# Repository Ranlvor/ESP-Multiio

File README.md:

Mechanical
==========

Achtung: Eines der Haltelöscher ist nicht 5mm / 5mm vom Rand entfernt! Das 3D-Druck-Gehäuse geht davon aus, dass alle Löscher 5mm/5mm vom Rand entfernt sind und muss noch angepasst werden.

BOM
===

zwingend Nötig
--------------

Bezeichnung | Beschreibung
------------|--------------
U1          | Wemos D1 Mini

notwendig für LEDs und Schalter
-------------------------------

Bezeichnung                    | Beschreibung                        | Package
-------------------------------|-------------------------------------|-----------------
D1, D2, D3, D4, D5, D6, D7, D8 | LEDs                                | 3mm Through Hole
R1, R2, R3, R4, R5, R6, R7, R8 | Vorwiderstände passend zu den LEDs  | 1206 SMD
U2                             | MCP23017                            | DIP-28
C1                             | Kondensator ca. 100 nF              | 1206 SMD

notwendig für IR receive (getestet, hat nicht funktioniert)
-----------------------------------------------------------

Bezeichnung | Beschreibung                        | Package
------------|-------------------------------------|-----------------
U4          | TL1838                              | TSOP1838
C2          | Kondensator ca. 100 nF              | 1206 SMD
R11         | Widerstand 33 kΩ                    | 1206 SMD
R12         | Widerstand 100 Ω                    | 1206 SMD

notwendig für IR send (ungetestet)
----------------------------------

Bezeichnung | Beschreibung                        | Package
------------|-------------------------------------|-----------------
D-IR1       | IR-LED                              | 3mm Through Hole
Q1          | NPN-Transistor (z.B. BC337)         | TO-92
R10         | Widerstand 53 Ω                     | 1206 SMD
R9          | Widerstand 2.1 kΩ                   | 1206 SMD

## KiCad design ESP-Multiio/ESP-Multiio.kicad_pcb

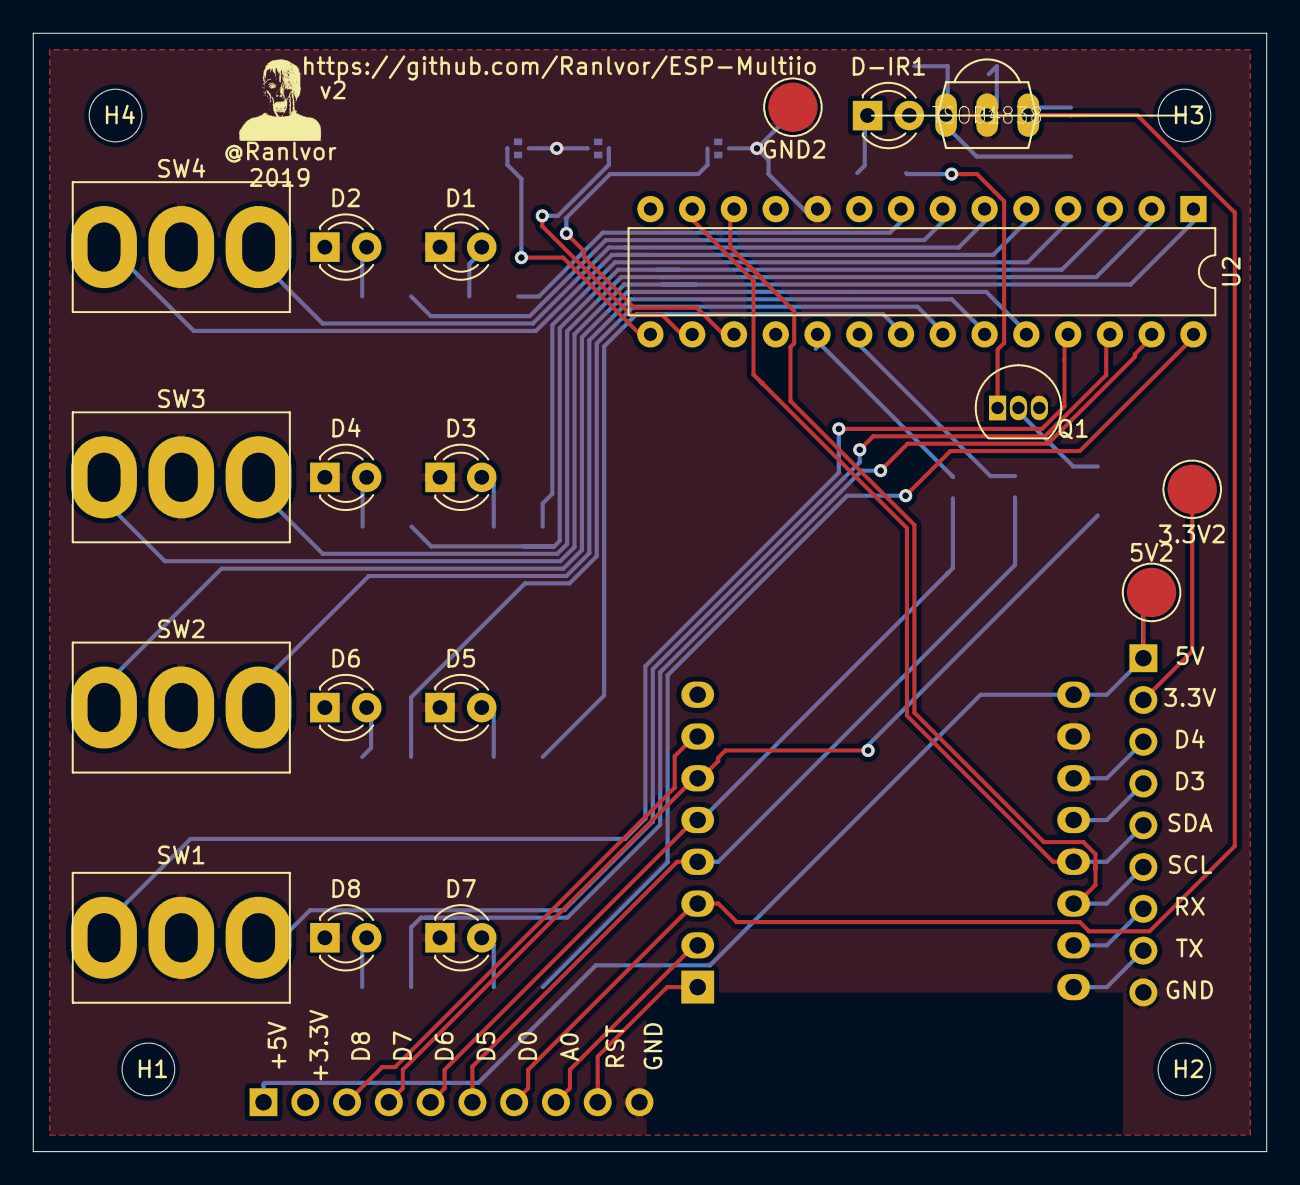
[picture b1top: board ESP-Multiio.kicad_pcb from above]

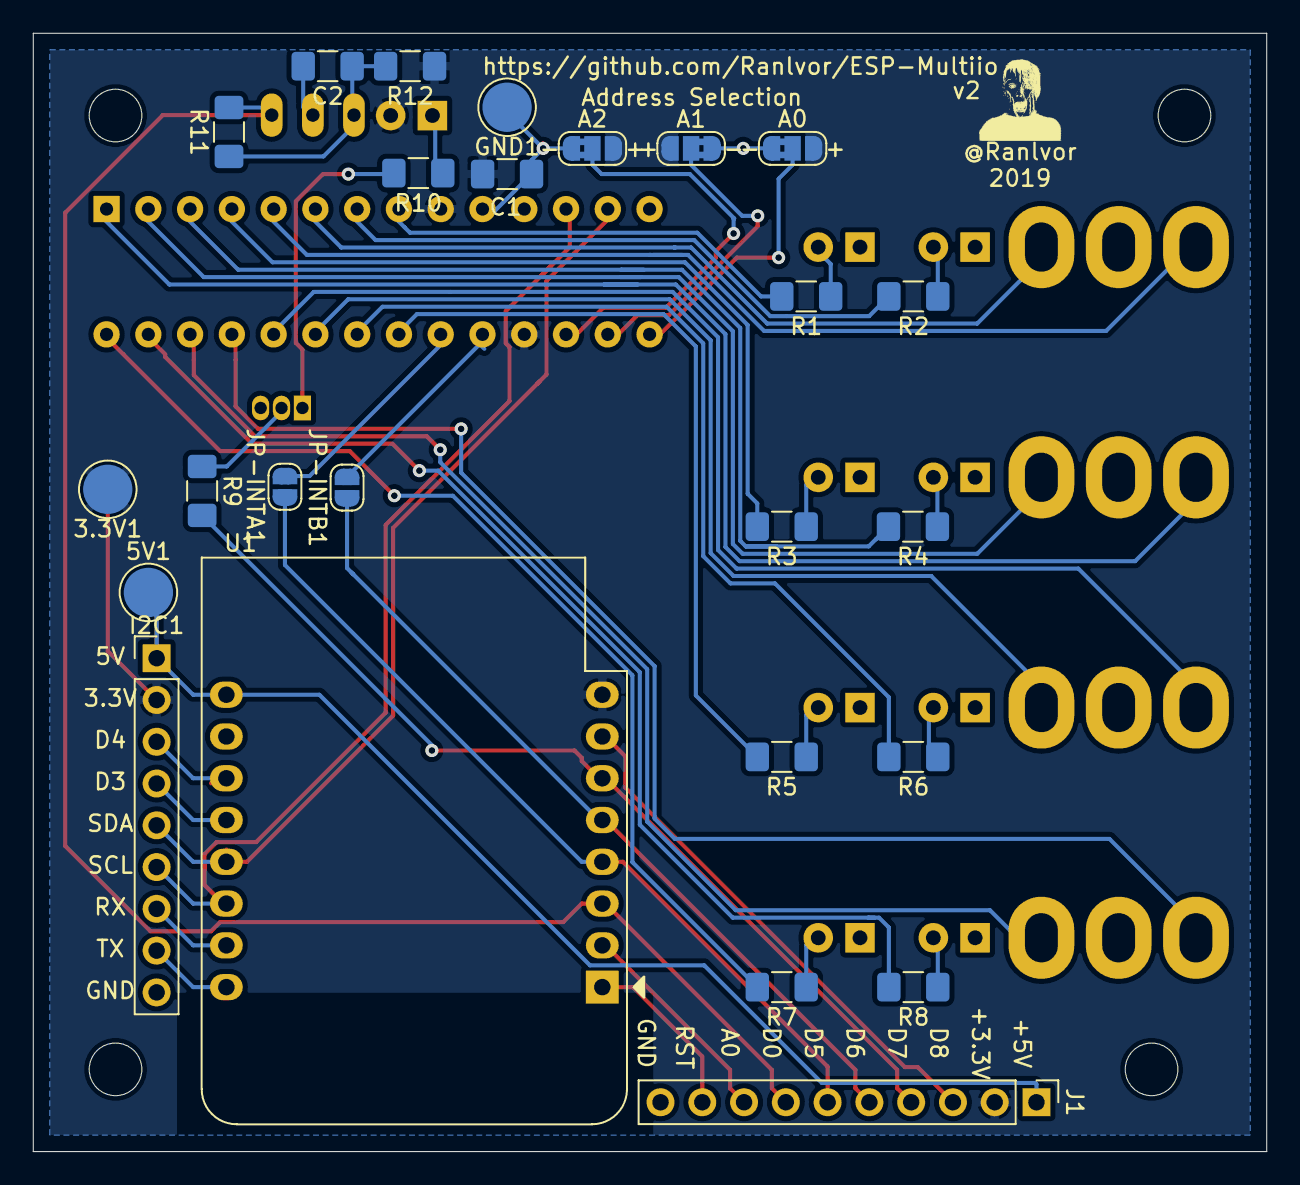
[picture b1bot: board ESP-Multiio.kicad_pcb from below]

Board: 2 copper layers, 75.0 x 68.0 mm, 48 parts (25 on the bottom side), 49 nets.

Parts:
3.3V1, 3.3V2, 5V1, 5V2: TestPoint; TestPoint_Pad_D3.0mm
A0, A1, A2: SolderJumper; SolderJumper-3_P1.3mm_Bridged2Bar12_RoundedPad1.0x1.5mm_Num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
C1, C2: 100 nF; C_1206_3216Metric_Pad1.42x1.75mm_HandSolder
D1, D2, D3, D4, D5, D6, D7, D8: LED; LED_D3.0mm
D-IR1: LED; LED_D3.0mm
GND1, GND2: TestPoint; TestPoint_Pad_D3.0mm
H1, H2, H3, H4: MountingHole; MountingHole_3.2mm_M3
I2C1: Conn_01x09; PinHeader_1x09_P2.54mm_Vertical
J1: Conn_01x10; PinHeader_1x10_P2.54mm_Vertical
JP-INTA1: SolderJumper_2_Open; SolderJumper-2_P1.3mm_Open_RoundedPad1.0x1.5mm
JP-INTB1: SolderJumper_2_Open; SolderJumper-2_P1.3mm_Open_RoundedPad1.0x1.5mm
Q1: BC337; TO-92_Inline
R1, R2, R3, R4, R5, R6, R7, R8: R; R_1206_3216Metric_Pad1.42x1.75mm_HandSolder
R9: 2.1kΩ; R_1206_3216Metric_Pad1.42x1.75mm_HandSolder
R10: 53 Ω; R_1206_3216Metric_Pad1.42x1.75mm_HandSolder
R11: 33 kΩ; R_1206_3216Metric_Pad1.42x1.75mm_HandSolder
R12: 100Ω; R_1206_3216Metric_Pad1.42x1.75mm_HandSolder
SW1, SW2, SW3, SW4: SW_SPDT_MSM; MTS-103
U1: WeMos_D1_mini; WEMOS_D1_mini_light
U2: MCP23017_SP; DIP-28_W7.62mm
U4: TSOP1838; TSOP18XX

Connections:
+3V3: 3.3V1.1, 3.3V2.1, A0.3, A1.3, A2.3, C1.1, D-IR1.2, I2C1.2, J1.2, R12.1, U1.8, U2.9, U2.18
+5V: 5V1.1, 5V2.1, I2C1.1, J1.1, U1.9
/A0: J1.8, U1.2
/D0: J1.7, R11.2, U1.3, U4.OUT
/D5: J1.6, JP-INTA1.1, U1.4
/D6: J1.5, JP-INTB1.1, U1.5
/D7: J1.4, R9.2, U1.6
/D8: J1.3, U1.7
/GPA0: R1.2, U2.8
/GPA1: R2.2, U2.7
/GPA2: SW4.1, U2.6
/GPA3: SW4.3, U2.5
/GPA4: R3.2, U2.4
/GPA5: R4.2, U2.3
/GPA6: SW3.1, U2.2
/GPA7: SW3.3, U2.1
/GPB0: R7.2, U2.28
/GPB1: R8.2, U2.27
/GPB2: SW1.1, U2.26
/GPB3: SW1.3, U2.25
/GPB4: SW2.3, U2.24
/GPB5: SW2.1, U2.23
/GPB6: R6.2, U2.22
/GPB7: R5.2, U2.21
/RST: J1.9, U1.1
/RX: I2C1.7, U1.15
/TX: I2C1.8, U1.16
D3: I2C1.4, U1.12
D4: I2C1.3, U1.11
GND: A0.1, A1.1, A2.1, C1.2, C2.2, D1.1, D2.1, D3.1, D4.1, D5.1, D6.1, D7.1, D8.1, GND1.1, GND2.1, I2C1.9, J1.10, Q1.3, SW1.2, SW2.2, SW3.2, SW4.2, U1.10, U2.10, U4.GND
unnamed: A0.2, U2.15
unnamed: A1.2, U2.16
unnamed: A2.2, U2.17
unnamed: C2.1, R11.1, R12.2, U4.VCC
unnamed: D1.2, R1.1
unnamed: D2.2, R2.1
unnamed: D3.2, R3.1
unnamed: D4.2, R4.1
unnamed: D5.2, R5.1
unnamed: D6.2, R6.1
unnamed: D7.2, R7.1
unnamed: D8.2, R8.1
unnamed: D-IR1.1, R10.1
unnamed: JP-INTA1.2, U2.20
unnamed: JP-INTB1.2, U2.19
unnamed: Q1.1, R10.2
unnamed: Q1.2, R9.1
SCL: I2C1.6, U1.14, U2.12
SDA: I2C1.5, U1.13, U2.13

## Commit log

2019-06-07 Better switch-footprint, add twitter avatar, add github link
2019-06-08 more 3.3V fill
2019-06-10 Change board dimensions
    Because the switches need to be further appart
2019-06-10 Mechanical Details, Mechanical data in Silkscreen
2019-06-10 More fill
2019-06-15 Add gerber code, more gehäuse-stuff
2019-06-16 Gehäuse: Add Bottom part
2019-06-19 First Version of Gehäuse
2019-06-19 After first testprint: put in screw deeper because my screws are a bit short
2019-06-22 Add flatmode
2019-06-22 Fix wiring in flat mode
    The cable has to go on top of the board in flat mode instead of below the board
2019-07-02 Don't break build because a part of the model didn't build
2019-07-05 allow rendering cuts of the gehäuse
2019-07-05 Further gehäuse cut improvements
    - rotate cut to fit preview
    - higher resolution
    - top/bottom-combination-view
2019-07-05 one layer of plastic in switch screw hole
    to make it printable without support
2019-07-05 Deeper screw holes
    to allow us to use the shorter screw
2019-07-05 lower the text into the surface
    to get a flat surface to be able to print it
2019-07-07 chamfers on the top instead of fillets
    because current plan is to print the top face down and that does not work with fillets.
2019-07-07 Weniger rundung
    weil zu viel rundung mit chamfers einfach kacke aussieht
2019-07-07 bigger previews for more details
2019-07-12 Add IR sender LED
2019-08-08 Ignore some stuff
2019-08-08 Flip two parts on board to lower casing hight
2019-08-08 generate gerber v2
2019-08-08 remove non-flat-mode-support
2019-08-08 reduce spaceBottom
    The big transistor is gone, we just need 5 mm for the capacitors and the mounting screws
2019-08-08 Makefile: no flat mode either
2019-09-04 First README-Draft
